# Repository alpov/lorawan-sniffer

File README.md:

# LoRaWAN Traffic Analysis Tools

This repository contains the tools and materials used to obtain the dataset analyzed in the paper *[Exploring LoRaWAN Traffic: In-Depth Analysis of IoT Network Communications](https://www.mdpi.com/1424-8220/23/17/7333)*, dataset available in 
.

The sniffer hardware comprises three IMST ic880A modules, connected to a Raspberry Pi along with a GPS and RTC. The signal path from the antenna includes a SAW filter, an LNA, and a four-way power splitter. The documentation for the motherboard hardware including several photos can be found in the `eagle` folder.

The Raspberry Pi mini-computer runs Raspberry Pi OS Lite. The ic880A modules connect via the SPI interface, the GPS through UART, and the RTC through I2C. Forks of the `lora_gateway` and `packet_forwarder` projects have been modified to support multiple SPI interfaces and the required sniffer functions (receiving packets with inverted IQ, no CRC, implicit header). Table 1 presents a list of the impacted SX1301 registers. A fork of the `ttybus` project provides GPS receiver hub support for all three instances of `packet_forwarder`, including correct GPS initialization. Configuration files and `systemd` scripts reside in the `packet_forwarder` repository.

Logs are stored on an SD card in JSON data format. For processing, we've developed a set of conversion tools to convert the raw JSON data recorded by the sniffer into the standard `pcap` format for Wireshark, using the [LoRaTap version 1](https://github.com/eriknl/LoRaTap) encapsulation implemented in recent Wireshark versions, which are available through the [automated build system](https://www.wireshark.org/download/automated/win64/) (choose 4.1.0rc0). The `pcap` data is then filtered, exported to `csv` format by the `tshark` tool, and post-processed using Python scripts. MATLAB scripts process the output data to provide graphical representations of statistics.

Therefore, the processing follows these steps:

* `01-compile.sh`: Compilation of conversion tools.
* `02-convert.sh`: Splitting the main log into individual datasets and converting to `pcap` format.
* `03-grep.sh`: Helper listings for specifying line numbers to split the log.
* `04-scan.sh`: Helper listings to determine line numbers to split the log.
* `05-count-packet.sh`: Statistics for individual packet types.
* `06-tshark-packet.sh`: Conversion to `csv` format and post-processing.
* `07-csv-devaddr.sh`: Assignment of network operators based on `DevAddr`.
* `08-csv-joinreq.sh`: Assignment of end device manufacturers based on `DevEUI`.
* `09-tshark-beacon.sh`: Class-B beacon analysis and processing of GPS data broadcast by the gateway.
* `run.m`: Generation of graphical statistics in MATLAB.

Example screenshot of Wireshark with decrypted _confirmed data up_ frame from `03_Brno_join.pcap` source:

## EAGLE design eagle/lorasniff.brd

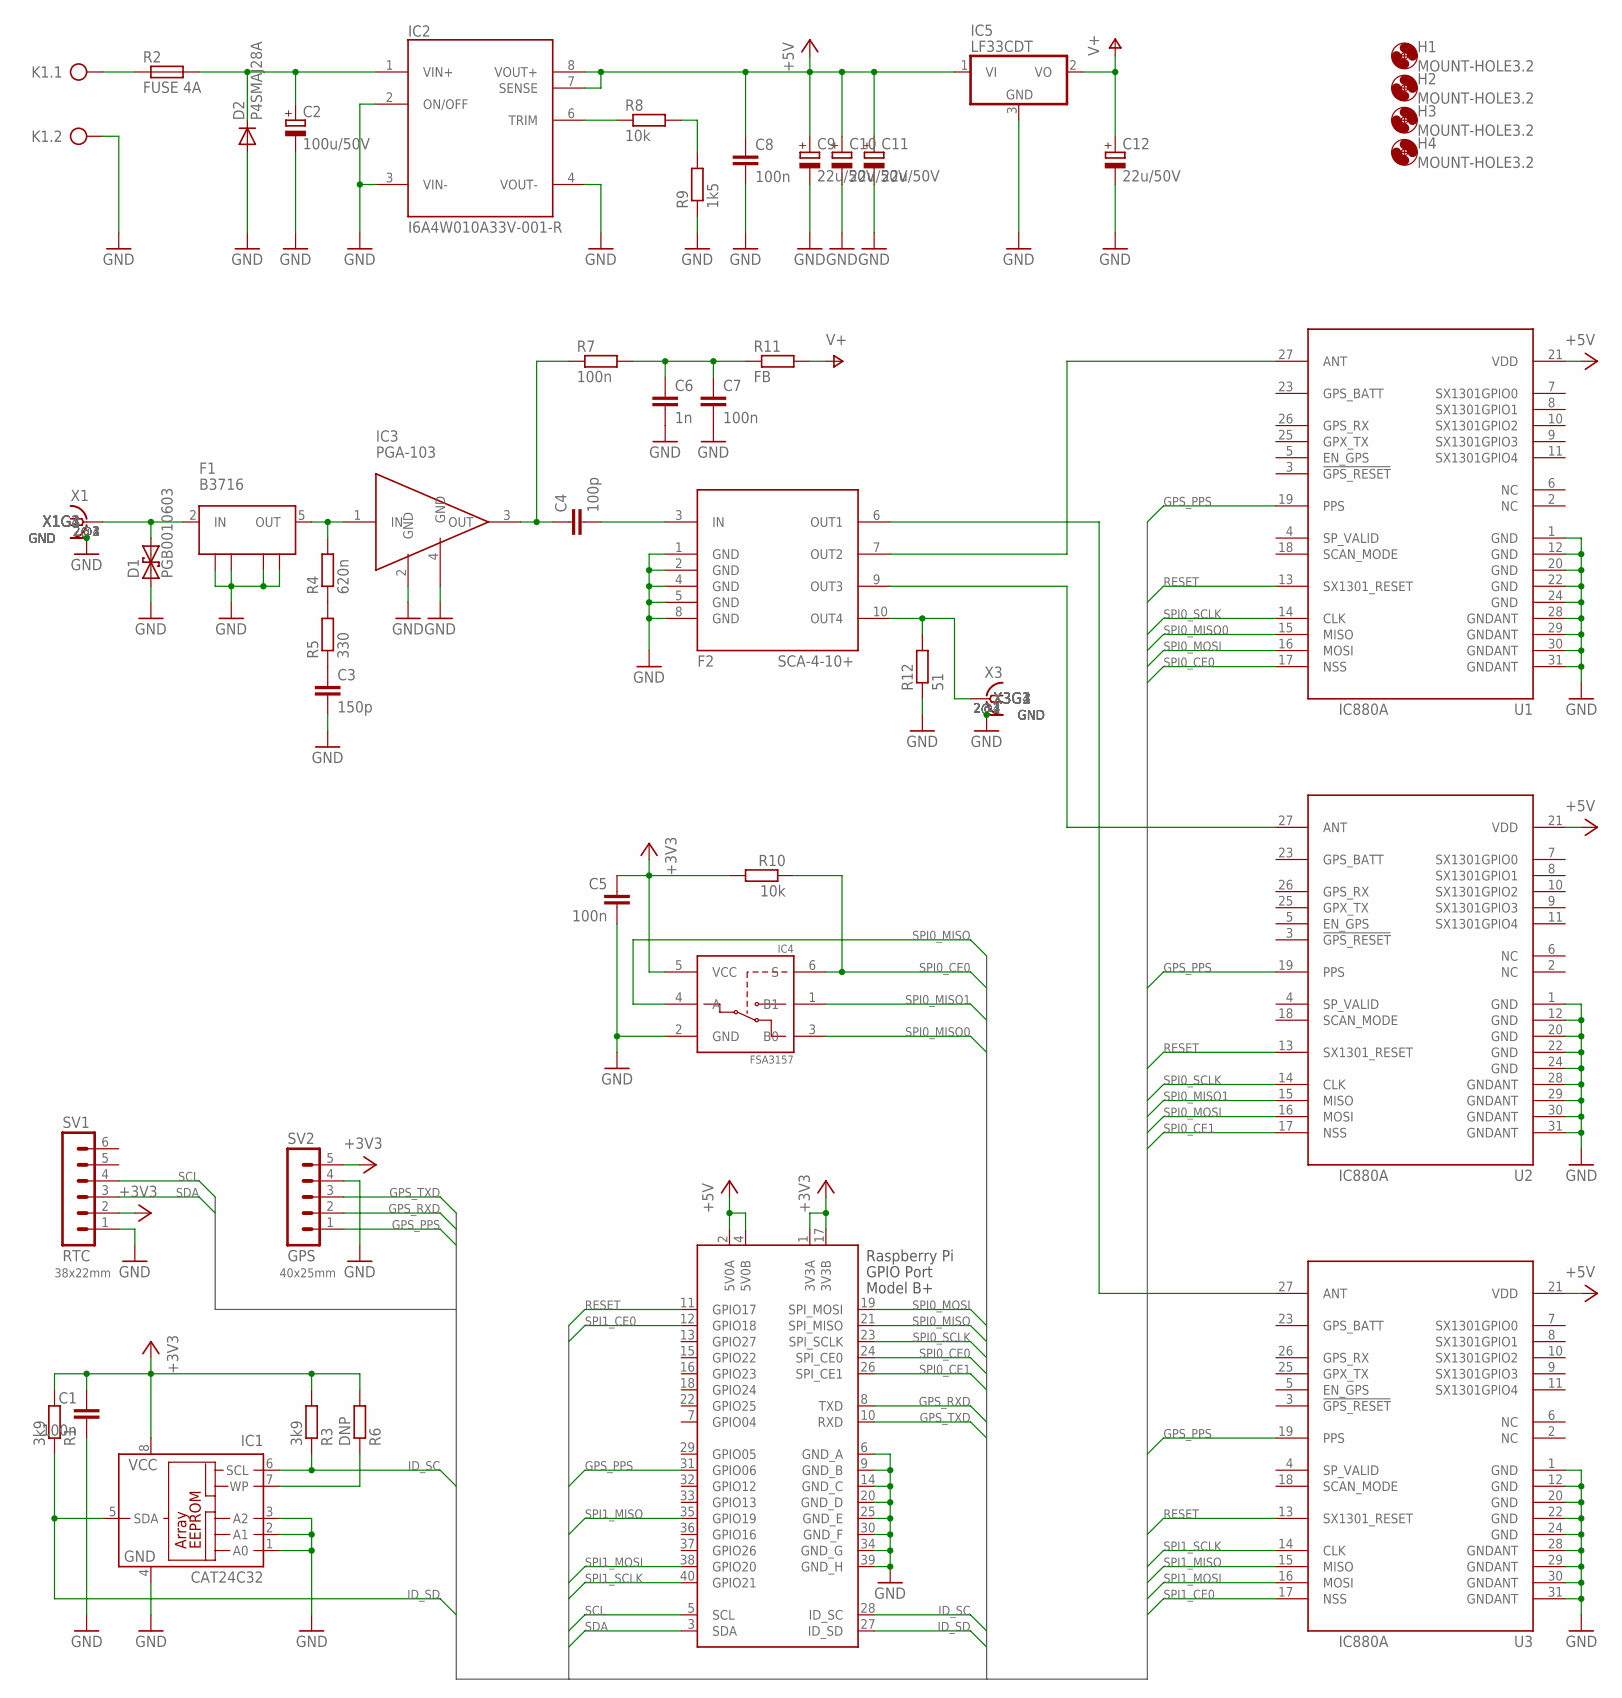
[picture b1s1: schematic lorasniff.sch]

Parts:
C1, C5, C7, C8: 100n; C0603K
C2: 100u/50V; E5-10,5
C3: 150p; C0603K
C4: 100p; C0603K
C6: 1n; C0603K
C9, C10, C11, C12: 22u/50V; E2,5-5
D1: PGB0010603; 0603
D2: P4SMAJ28A; DO214AC
F1: B3716; DCC6C
F2: SCA-4-10+
H1, H2, H3, H4: MOUNT-HOLE3.2; 3,2
IC1: CAT24C32; SO-08
IC2: I6A4W010A33V-001-R; I6A4W
IC3: PGA-103; SOT89
IC4: FSA3157; SC70-6L
IC5: LF33CDT; TO252
K1: ARK950H/2
R1, R3: 3k9; R0603
R2: FUSE 4A; R1206
R4: 620n; R0603
R5: 330; R0603
R6: DNP; R0603
R7: 100n; R0603
R8, R10: 10k; R0603
R9: 1k5; R0603
R11: FB; R0603
R12: 51; R0603
SV1: RTC; MA06-1
SV2: GPS; MA05-1
U1, U2, U3: IC880A
X1, X3: SMA-DX-L; BU-SMA-L
X2: RASPI_BOARD_B+#_FP; RASPI_BOARD_B+_FULL_PAD

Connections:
+3V3: C1.1, C5.1, IC1.8 (VCC), IC4.5 (VCC), R1.2, R3.2, R6.2, R10.2, SV1.2, SV2.5, X2.1 (3V3A), X2.17 (3V3B)
+5V: C8.1, C9.+, C10.+, C11.+, IC2.7 (SENSE), IC2.8 (VOUT+), IC5.1 (VI), U1.21 (VDD), U2.21 (VDD), U3.21 (VDD), X2.2 (5V0A), X2.4 (5V0B)
GND: C1.2, C2.-, C3.2, C5.2, C6.2, C7.2, C8.2, C9.-, C10.-, C11.-, C12.-, D1.1, D2.A, F1.1 (GND), F1.3 (GND1), F1.4 (GND2), F1.6 (GND3), F2.1 (GND), F2.2 (GND), F2.4 (GND), F2.5 (GND), F2.8 (GND), IC1.1 (A0), IC1.2 (A1), IC1.3 (A2), IC1.4 (GND), IC2.2 (ON/OFF), IC2.3 (VIN-), IC2.4 (VOUT-), IC3.2 (GND), IC3.4 (GND), IC4.2 (GND), IC5.3 (GND), K1.2, R9.1, R12.1, SV1.1, SV2.4, U1.1 (GND), U1.12 (GND), U1.20 (GND), U1.22 (GND), U1.24 (GND), U1.28 (GNDANT), U1.29 (GNDANT), U1.30 (GNDANT), U1.31 (GNDANT), U2.1 (GND), U2.12 (GND), U2.20 (GND), U2.22 (GND), U2.24 (GND), U2.28 (GNDANT), U2.29 (GNDANT), U2.30 (GNDANT), U2.31 (GNDANT), U3.1 (GND), U3.12 (GND), U3.20 (GND), U3.22 (GND), U3.24 (GND), U3.28 (GNDANT), U3.29 (GNDANT), U3.30 (GNDANT), U3.31 (GNDANT), X1.2@1 (GND), X1.2@2 (GND), X1.2@3 (GND), X1.2@4 (GND), X2.6 (GND_A), X2.9 (GND_B), X2.14 (GND_C), X2.20 (GND_D), X2.25 (GND_E), X2.30 (GND_F), X2.34 (GND_G), X2.39 (GND_H), X3.2@1 (GND), X3.2@2 (GND), X3.2@3 (GND), X3.2@4 (GND)
GPS_PPS: SV2.1, U1.19 (PPS), U2.19 (PPS), U3.19 (PPS), X2.31 (GPIO06)
GPS_RXD: SV2.2, X2.8 (TXD)
GPS_TXD: SV2.3, X2.10 (RXD)
ID_SC: IC1.6 (SCL), R3.1, X2.28 (ID_SC)
ID_SD: IC1.5 (SDA), R1.1, X2.27 (ID_SD)
unnamed: C2.+, D2.C, IC2.1 (VIN+), R2.2
unnamed: F2.9 (OUT3), U2.27 (ANT)
unnamed: C4.2, F2.3 (IN)
unnamed: IC1.7 (WP), R6.1
unnamed: C4.1, IC3.3 (OUT), R7.1
unnamed: D1.2, F1.2 (IN), X1.1
unnamed: R4.1, R5.2
unnamed: C3.1, R5.1
unnamed: F1.5 (OUT), IC3.1 (IN), R4.2
unnamed: F2.10 (OUT4), R12.2, X3.1
unnamed: C6.1, C7.1, R7.2, R11.1
unnamed: F2.7 (OUT2), U1.27 (ANT)
unnamed: F2.6 (OUT1), U3.27 (ANT)
unnamed: K1.1, R2.1
unnamed: IC2.6 (TRIM), R8.1
unnamed: R8.2, R9.2
RESET: U1.13 (SX1301_RESET), U2.13 (SX1301_RESET), U3.13 (SX1301_RESET), X2.11 (GPIO17)
SCL: SV1.4, X2.5 (SCL)
SDA: SV1.3, X2.3 (SDA)
SPI0_CE0: IC4.6 (S), R10.1, U1.17 (NSS), X2.24 (SPI_CE0)
SPI0_CE1: U2.17 (NSS), X2.26 (SPI_CE1)
SPI0_MISO: IC4.4 (A), X2.21 (SPI_MISO)
SPI0_MISO0: IC4.3 (B0), U1.15 (MISO)
SPI0_MISO1: IC4.1 (B1), U2.15 (MISO)
SPI0_MOSI: U1.16 (MOSI), U2.16 (MOSI), X2.19 (SPI_MOSI)
SPI0_SCLK: U1.14 (CLK), U2.14 (CLK), X2.23 (SPI_SCLK)
SPI1_CE0: U3.17 (NSS), X2.12 (GPIO18)
SPI1_MISO: U3.15 (MISO), X2.35 (GPIO19)
SPI1_MOSI: U3.16 (MOSI), X2.38 (GPIO20)
SPI1_SCLK: U3.14 (CLK), X2.40 (GPIO21)
V+: C12.+, IC5.2 (VO), R11.2

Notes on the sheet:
40x25mm
38x22mm

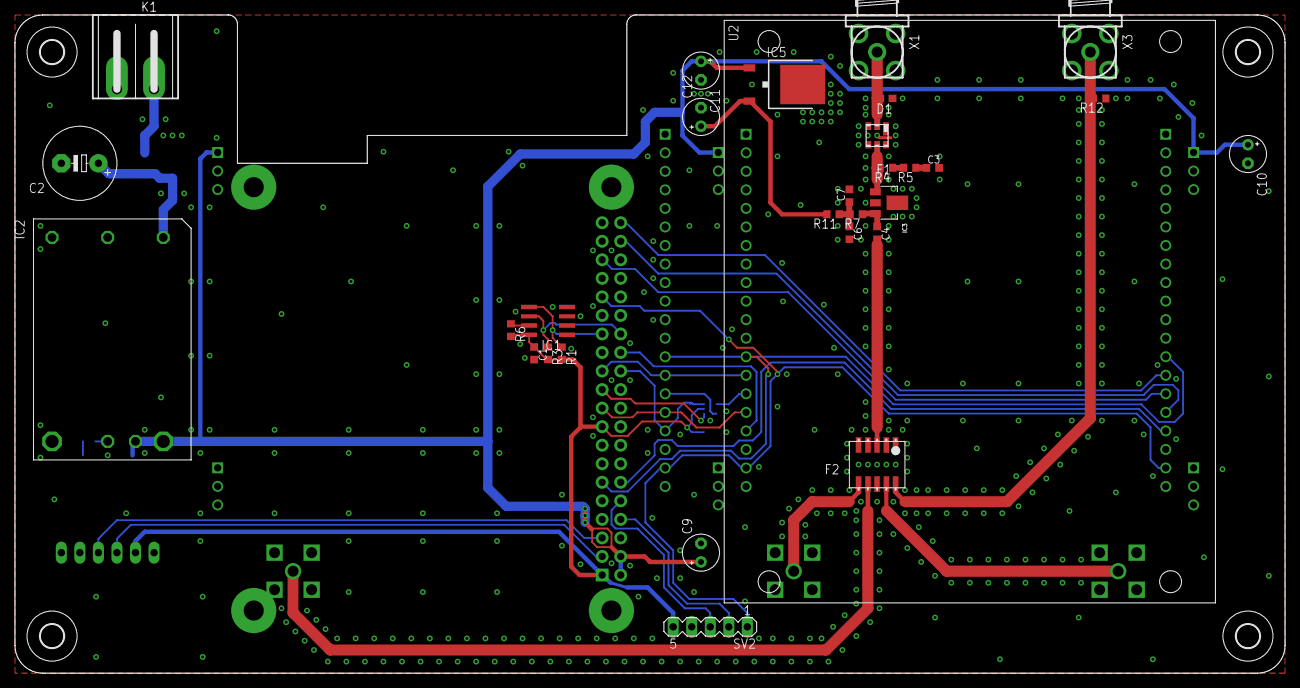
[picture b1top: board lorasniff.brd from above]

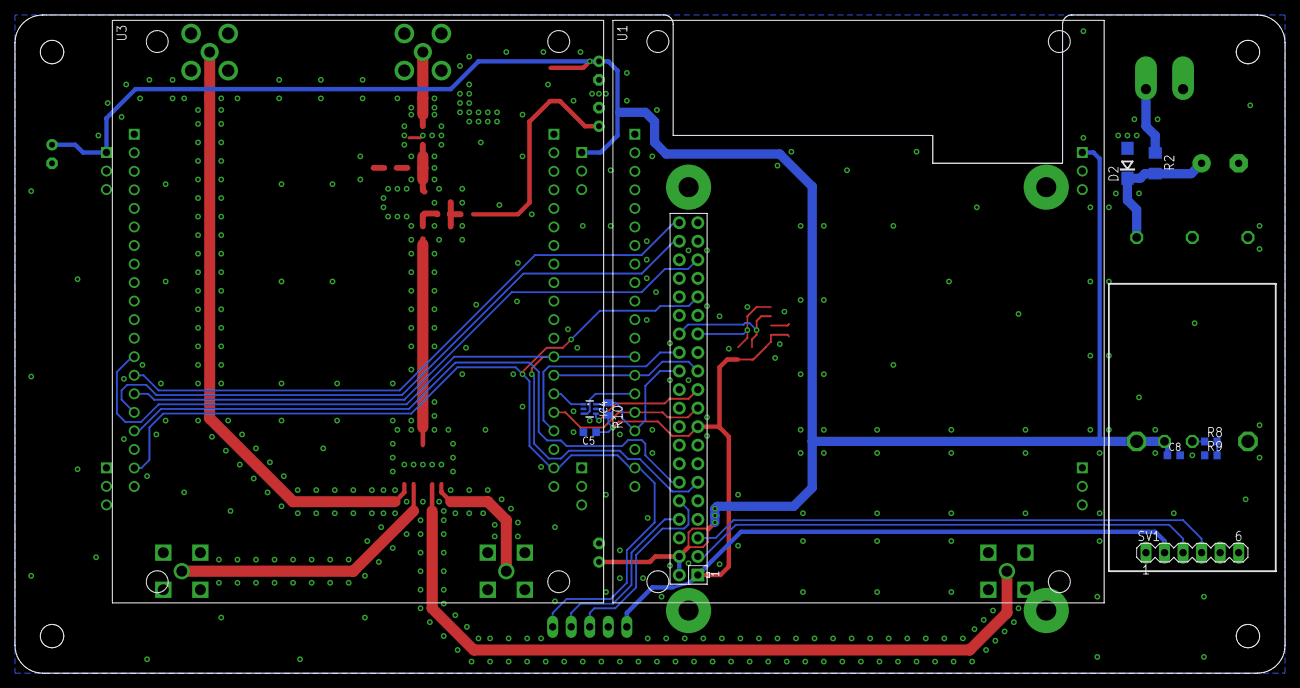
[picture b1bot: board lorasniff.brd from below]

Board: 2 copper layers, 174.0 x 90.2 mm, 46 parts (12 on the bottom side), 39 nets.

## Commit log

2023-05-09 Initial upload
2023-05-17 Added unassigned to lists, added totals, fixed legend positions, fixed +x
2023-05-25 Fixed channel order in MATLAB scripts
2023-06-28 Fixed timeshift in MATLAB, added note about Wireshark version to README.md
2023-06-28 Moved cJSON library to submodule
2023-07-12 Update README.md, added photos
2023-08-28 Updated MATLAB figures, updated links
